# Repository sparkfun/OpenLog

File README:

OpenLog is an open source project to create a simple to use data logger. 

OpenLog v1 is stable but only supports FAT16 and up to 2GB.
OpenLog v2 is a bit buggy but supports FAT32 and SD cards up to 16GB.
OpenLog v3 is stable, supports FAT32 and supports higher record speeds (115200/57600).

The hardware design and firmware are released under CC-SA v3 license.
The FAT16/FAT32 firmware was originally designed by Roland Riegel and is released under GPL v2.
OpenLog v2.0 and above uses sdfatlib written by Bill Greiman and is released under GPL v3.
The OpenLog firmware was created by SparkFun Electronics.

v1.0 Buggy initial release
v1.1 Small changes to system settings and EEPROM storage.
v1.2 Added wild card to listing and remove commands. Added read file command.
v1.3 Added auto buffer record if unit sits idle for more than 5 seconds.
v1.4 Increase buffer size to 900 bytes. Pinning down URU errors.
v1.5 Lowered power consumption to ~2mA avg. Added 4800 and 19200 baud rates.
v1.51 Added configurable escape character, and escape character amount.
v1.6 Added ability to configure via config.txt file.
v2.0 Massive overhaul. Ported to sdfatlib. Now supports FAT16/FAT32/SD/SDHC.
v2.1 Power save not working. Fixed issue 35. Dropping characters at 57600bps.
v2.11 Tested with 16GB microSD. Fixed issues 30 & 34. Re-enable power save.
v2.2 Modified append_file() to use a single buffer. Increased HardwareSerial.cpp buffer to 512 bytes.
v2.21 ringp fork brought in. rm dir, cd .., and wildcards now work!
v2.3 Migrated to v10.10.10 of sdfatlib. Moved to inline RX interrupt and buffer.
v2.4 Merged ringp updates. Commands cd, rm, ls work again!
v2.41 Power loss bug fixed. Adding support for 38400bps for testing with SparkFum 9DOF IMU logging. 
v2.5 Added software reset command. Modified the read command to print extended ASCII characters.
v2.51 Changed command prompt control to ignore \n for easier control from microcontroller.
v3.0 Migration to Arduino v1.0 and better recording speed at 115200bps and 57600bps.

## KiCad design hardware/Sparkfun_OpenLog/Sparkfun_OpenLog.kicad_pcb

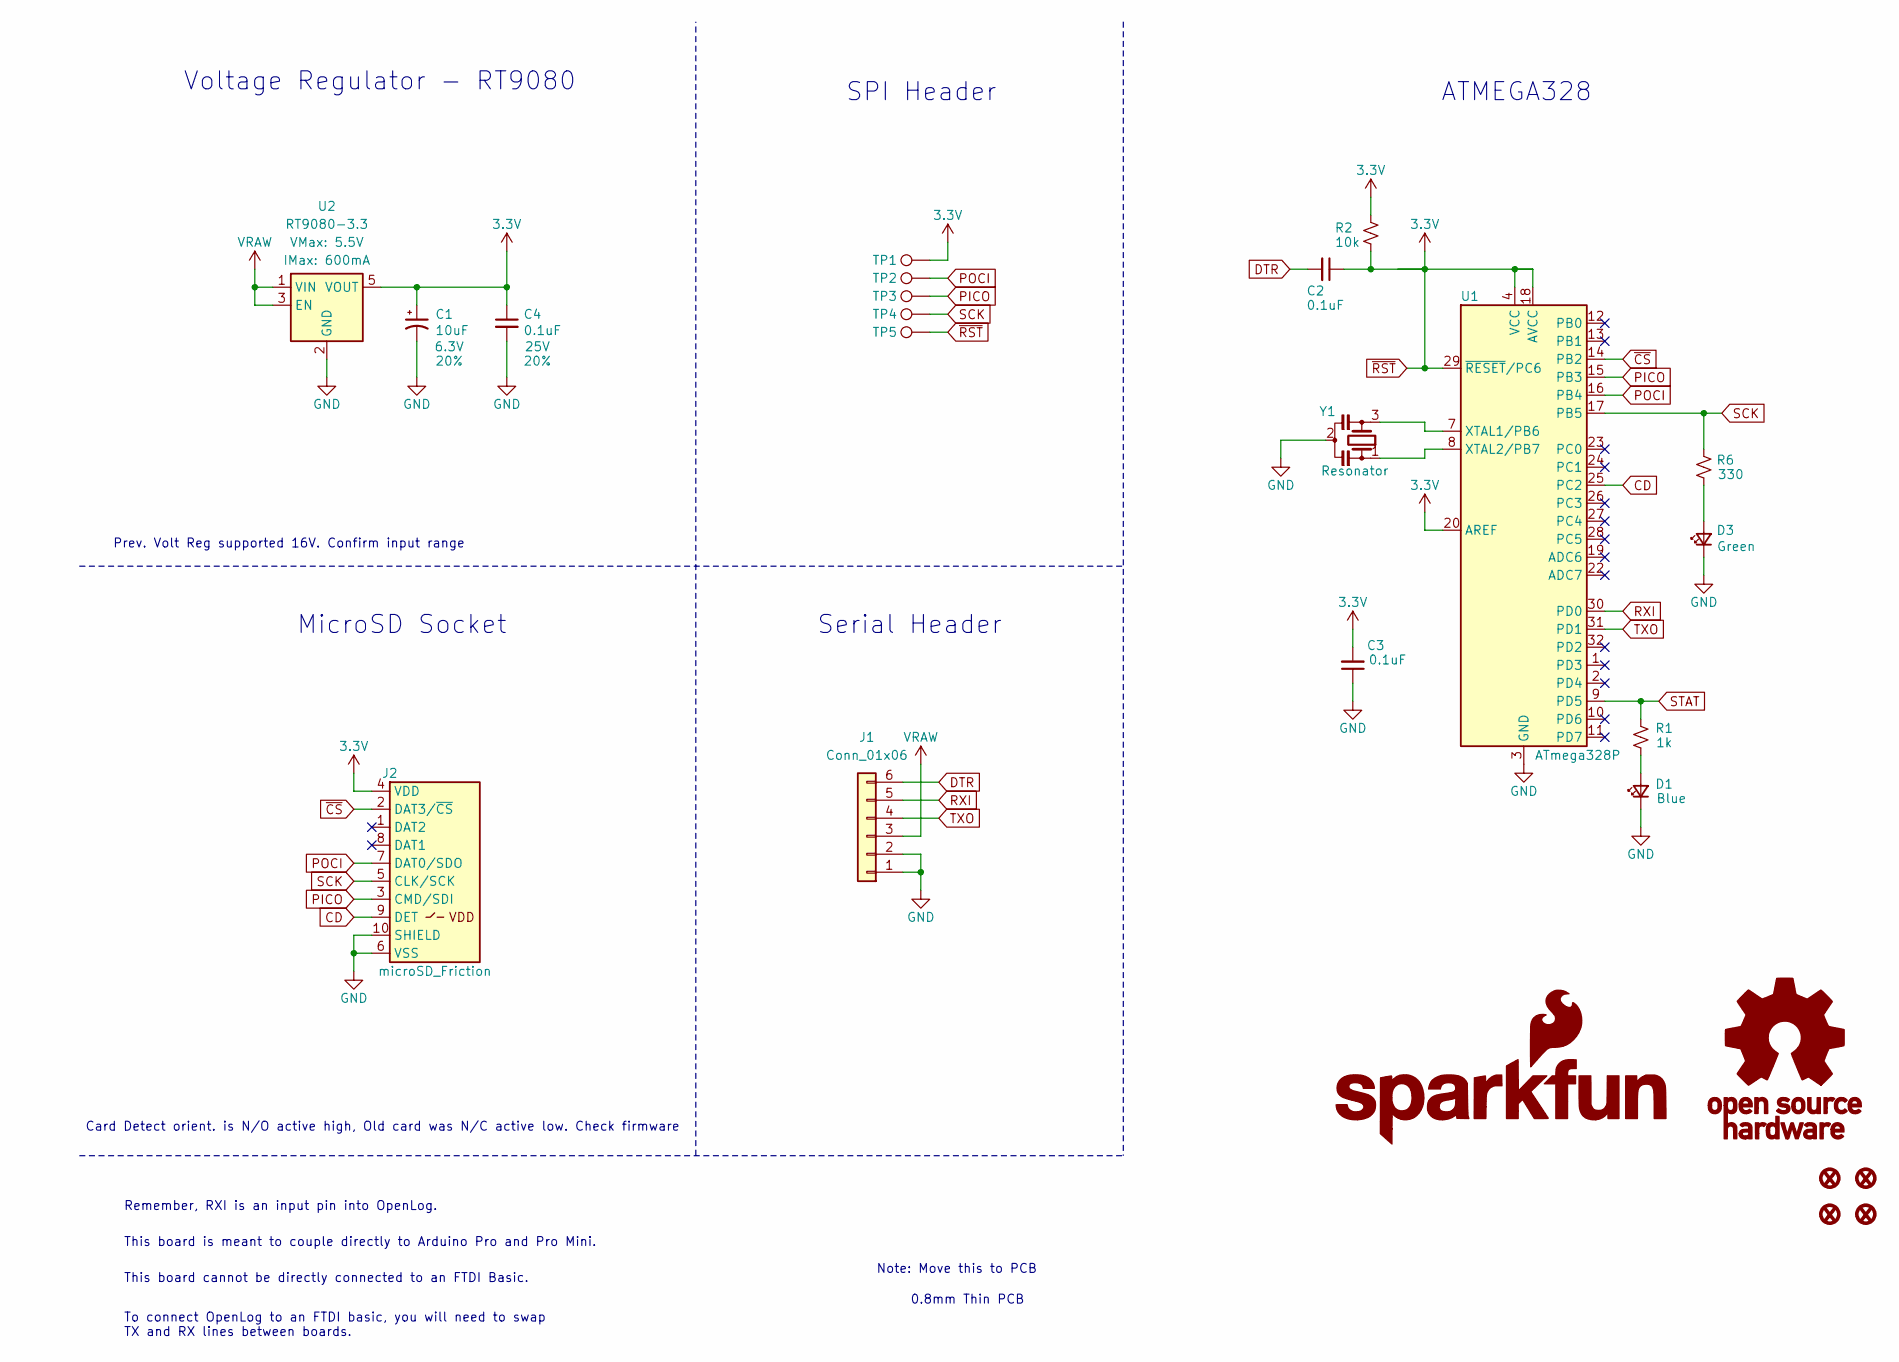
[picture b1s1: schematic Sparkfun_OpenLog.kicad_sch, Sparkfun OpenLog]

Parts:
C1: 10uF; C_0603_1608Metric_Polar; Voltage 6.3V; Tolerance 20%
C2, C3, C4: 0.1uF; C_0603_1608Metric; Voltage 25V; Tolerance 20%
D1: Blue; LED_0603_1608Metric_Blue
D3: Green; LED_0603_1608Metric_Green
FID1, FID2, FID3, FID4: Fiducial_0.5mm; Fiducial_0.5mm_Mask1mm
G1: OSHW_Logo; Creative_Commons_License
G2: SparkFun_Logo
J1: Conn_01x06; 1x06_P2.54mm
J2: microSD_Friction; microSD_Friction_Fit_Common
R1: 1k; R_0603_1608Metric
R2: 10k; R_0603_1608Metric
R6: 330; R_0603_1608Metric
TP1, TP2, TP3, TP4, TP5: 1.25mm; TestPoint-1.25mm
U1: ATmega328P; TQFP-32_7x7mm_P0.8mm
U2: RT9080-3.3; SOT23-5
Y1: Resonator; Resonator_SMD_3.2x1.3mm

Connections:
CD: J2.9 (DET), U1.25 (PC2)
DTR: C2.2, J1.6
GND: C1.2, C3.1, C4.2, D1.1 (K), D3.1 (K), J1.1, J1.2, J2.6 (VSS), J2.10 (SHIELD), U1.3 (GND), U1.5 (GND), U1.21 (GND), U2.2 (GND), Y1.2
unnamed: D1.2 (A), R1.2
unnamed: D3.2 (A), R6.2
unnamed: U1.7 (XTAL1/PB6), Y1.3
unnamed: U1.8 (XTAL2/PB7), Y1.1
PICO: J2.3 (CMD/SDI), TP3.1, U1.15 (PB3)
POCI: J2.7 (DAT0/SDO), TP2.1, U1.16 (PB4)
RXI: J1.5, U1.30 (PD0)
SCK: J2.5 (CLK/SCK), R6.1, TP4.1, U1.17 (PB5)
STAT: R1.1, U1.9 (PD5)
TXO: J1.4, U1.31 (PD1)
VRAW: J1.3, U2.1 (VIN), U2.3 (EN)
~CS: J2.2 (DAT3/~CS), U1.14 (PB2)
~RST: C1.1, C2.1, C3.2, C4.1, J2.4 (VDD), R2.1, R2.2, TP1.1, TP5.1, U1.4 (VCC), U1.6 (VCC), U1.18 (AVCC), U1.20 (AREF), U1.29 (~RESET/PC6), U2.5 (VOUT)

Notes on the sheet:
Remember, RXI is an input pin into OpenLog.
Card Detect orient. is N/O active high, Old card was N/C active low. Check firmware
Prev. Volt Reg supported 16V. Confirm input range
Note: Move this to PCB
0.8mm Thin PCB
Voltage Regulator - RT9080
MicroSD Socket
This board is meant to couple directly to Arduino Pro and Pro Mini.
This board cannot be directly connected to an FTDI Basic.
ATMEGA328
To connect OpenLog to an FTDI basic, you will need to swap TX and RX lines between boards.
SPI Header
Serial Header

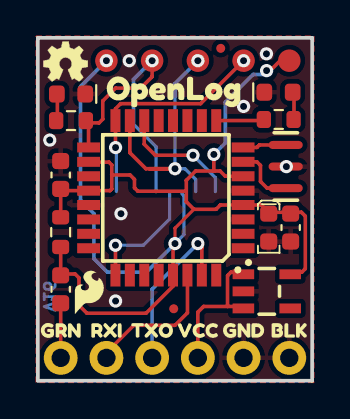
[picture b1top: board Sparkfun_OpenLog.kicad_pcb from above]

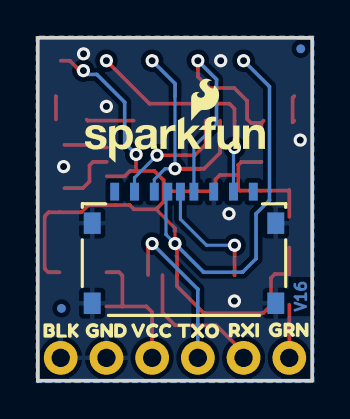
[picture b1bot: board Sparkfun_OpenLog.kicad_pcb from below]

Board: 2 copper layers, 15.2 x 19.0 mm, 38 parts (9 on the bottom side), 16 nets.

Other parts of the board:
Ref**: Val**; OSHW_Logo_2.5mm
kibuzzard-69F1223A, kibuzzard-69F1223A#2: G***; kibuzzard-69F1223A
kibuzzard-69F1224C, kibuzzard-69F1224C#2: G***; kibuzzard-69F1224C
kibuzzard-69F1225D, kibuzzard-69F1225D#2: G***; kibuzzard-69F1225D
kibuzzard-69F1226C, kibuzzard-69F1226C#2: G***; kibuzzard-69F1226C
kibuzzard-69F12217, kibuzzard-69F12217#2: G***; kibuzzard-69F12217
kibuzzard-69F12278, kibuzzard-69F12278#2: G***; kibuzzard-69F12278
kibuzzard-69F12315: G***; kibuzzard-69F12315

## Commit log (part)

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2009-12-23 Test commit
2009-12-23 Posting main source
2009-12-24 Adding Eagle Files and some directory structure
2009-12-28 v1.1 - Fixes over-run resets and adds NewLog and SeqLog functions. Added lots-o-text.txt for testing.
2010-02-18 Split out the cluster offset calcuation to avoid a signed/unsigned 16x16 multiply breaking over 32k. I.E. create and set a u32, multiply it by the signed (sizeof), then add the offset.
2010-03-17 Added support for extended read command. The read command now accepts parameters for file position and number of characters to read.
2010-03-18 Version number (v1.2) to main.c. The number of write cycles to EEPROM minimized in order not to wear out the EEPROM memory. Other comment changes.
2010-03-23 Using "init" command to initialize the SD card will not reset file system handles stored in global arrays in fat.c. Calling "init" several times will cause other commands to stop working, like "cd <f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
2010-03-24 v1.3 Added sd_raw_sync() inside append_file. I believe this was why tz1's addition of the timeout buffer update feature was not working. Auto buffer update now working. So if you don't send anything 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
2010-03-31 v1.4 Eliminates errors while logging at 57600bps. Added exit options to the two menus (set and baud) Also added display of current settin to two menus (Ex: "Baud currently: 57600bps")
    Added '!' infront of 'error opening'. This pops up if there is an error while trying to append to a freshly created new log (ex: LOG00548.txt is created, then errors out because it cannot append). '!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
    Replicated logging errors at 57600 using 5V Arduino
    Unit would systematically glitch during logging of 111054 bytes
    Increasing buffer to 1000 characters caused URU error.
    URU: Unit Resets Unexpectedly
    To recreate URU error. Type "append ". Include the space. If you g
2010-04-07 v1.5 Added 4800bps and 19200bps support
    Added power saving features. Current consumption at 5V is now:
    In default append mode:
    6.6/5.5mA while receiving characters (LED On/Off)
    2.1mA during idle
    In command mode: 3.2/2.1mA (LED On/Off)
    So if you're actively throwing characters at the logger, it will be ~6mA. If you send the logger characters then delay 5-10 seconds, current will be ~2.5mA. (Unit records the characters in the buffer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
2010-04-21 v1.6 Adding config file. OpenLog can now be configured either through CONFIG.txt or through system menus.
    What happens if I reset the system by pulling RX low, but the config file has corrupt values in it? If config file has corrupt values in it, system will default to known values 9600/ctrl+z/3/newlog. 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
2010-06-01 Support for using OpenLog with Parallax Javelin Stamp. Simplified set of commands -that can be used with any other micro processor- to count files in a folder (efcount), get file info (efinfo), turn 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
2010-06-03 Fix for disabling the logging of escape character ASCII 26 (Ctrl+z). When appending to a file the escape character currently used will also be appended to the file. In order to avoid this problem iss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
2010-06-07 Fixed timing issue in OpenLog.java. Removed unnecessary delay in openLogExecute().
2010-08-04 v2.1 - Fixed issue 35. Dropping characters at 57600bps. Power save not working.
    26058 bytes out of 30720
    Fixed a bug found by Salient (Issue 35). User settings where declared at chars which allowed them to be signed. If a user went from old firmware, to v2, the safety checks would fail because the setti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
    Added "a) Clear user settings" to set menu. This allows us to completely wipe an OpenLog (user settings and config file) to see how it will respond to future firmware changes.
    Improved the file 'size' command.
    Sequential logging is tested and works.
    Receive testing: Using the Test_Sketch found on Github, I
2010-08-18 v2.11 Tested with 16GB microSD. Fixed some general bugs. Lowered power consumption.
    26136 bytes out of 30720
    Fixed issue 30. I added printing a period ('.') for non-visible ASCII characters during a 'read' command. This cleans up the output a bit. HEX printing is still available.
    Fixed issue 34. When issuing a long command such as "read log00056.txt 100 200 2" (read from spot 100 to spot 200 and print in HEX), the command shell would die at 24 spots. I increased both the gene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
    Works with a 16GB microSD card! High volume test: loaded 16GB card with 5GB of
2010-09-21 Makefile changes. Not to be commited upstream.
2010-09-26 Added support for removing an empty folder using "rm -f" command. Listing the contents of a folder lists the subfolders first and then the files in the folder.
2010-10-03 Fixed "888 88" bug when hitting backspace. Resolved ambigous "rm" command, new "rm" implementation. New commands: pwd (print working directory), echo <on>|<off>. Fixed bug when using "size", leaking 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
2010-10-27 Added .gitignore to ignore *.class and *.jpf files.
2010-11-03 v2.4 Merged ringp updates. Commands cd, rm, ls work again! New "rm -rf" command to remove directory and its files.
    Windows 7 stores the Arduino hex file is an aweful place. Something like:
    C:\Users\Main\AppData\Local\Temp\build3390340147786739225.tmp\OpenLog_v2.cpp.hex
    Added HardwareSerial.cpp and a readme to the main trunk.
    Added OpenLog_v2.cpp.hex to the main trunk.
2010-11-03 Missing HardwareSerial.h needed by HardwareSerial.cpp
    New function declarations in the HardwareSerial class needs the functions
    to be declarared in the h-file. This commit contains a modified version of the
    original HardwareSerial.h file.
2011-06-01 v2.51 Improved command prompt parsing (now ignores '\n')
    We now ignore the \n character when parsing characters from the command prompt. This makes it easier to create code on a microcontroller that correctly controls OpenLog. Previously, println or sprint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
    sprintf(buff, "new blah.txt\r");
    Serial.print(buff); //No println, use \r in string instead
    Also - added a CommandTest sketch to demonstrate how you can control OpenLog from a microcontroller / automate the command prompt
2012-02-06 make sure escape characters don't end up in the file in append mode (fixes: https://github.com/nseidle/OpenLog/issues/92 )
2012-02-22 Updated the CommandTest code to Arudino v1.0. I had to change the Serial.print(char(26)) to Serial.write(26). Also added more comments to top of code. File is now .ino.
2012-02-26 added "mv" aka "rename" support to openlog; backported from a more recent fatlib
2012-03-14 v3.0 Re-write of core functions. Support under Arduino v1.0. Now supports full speed 57600 and 115200bps! Lower standby power. 28354 bytes out of 32256. Update to new beta version of SerialPort lib f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
    Unzip 'SerialPortBeta20120106.zip' and
2012-03-16 v3.1 28692 of 32256 Added fix from issue 76: https://github.com/nseidle/OpenLog/issues/76 Added support for verbose and echo settings recorded to the config file and EEPROM.
2012-03-23 v3.1 Fixed bug where entire log data is lost when power is lost. Added fix from issue 76: https://github.com/nseidle/OpenLog/issues/76 Added support for verbose and echo settings recorded to the conf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
2012-03-27 v3.11 Added freeMemory support for RAM testing. This was taken from: http://arduino.cc/playground/Code/AvailableMemory Also updated HEX files for v3.11 and v3 Light
2013-01-08 Changes to attempt to free up RAM.
    Added printRam/freeRam function from Jeelabs. Many more F() uses.
    new_file now exits before it calls append_file. Removed global Sf file
    in an attempt to free up RAM. Didn't really help. Removed helper line
    from the config file. We need to bring this back but I'm not sure how.
2013-01-08 v3.13 Lots of RAM management. Works well.
    Receive buffer returned to its glory of being around 800 bytes. This is
    very good news. Changed the string compares from strings in RAM (strcmp)
    to strings located in flash memory(strcmp_P). Removal of strncmp(). Once
    migrated to PSTR, it makes it worse. Issue 106 was the key to all this.
2013-01-14 Better handling of max time before sync.
    There is a case where the user could be throwing non-stop data at the
    unit. The log won't be recorded because it never goes idle. This version
    adds/makes better the check of max time for the un-recorded buffer. Also
    moved from sprintf_P to strcpy_P for known file names.
2013-01-15 Cleaned up the help menu.
2013-01-21 Added a fix for issue 132
    Sending lots of binary, fast, causes the escape character to not
    properly get reset. Added a secondary reset of escape_chars_received to
    reset it. Works well. Also added a binary test sketch to test OpenLogs
    with binary at 115200bps.
2013-03-07 porting readme to markdown and prettyfying
2013-03-07 Cleanup readme files.
2013-03-14 Updated the .hex files to reflect v3.14 changes
    Created new COMBINED .hex file (bootloader and v3.14 sketch) and updated
    OpenLog_v3.cpp.hex to be consistent with v3.14
2013-04-08 Added ability to ignore RX.
    You can now ignore the state of RX at power up. See issue #150.
2013-04-08 Fixed rm issue #134. dlkeng is my new favorite person.
    Fixed issue #135: When removing files and there is a directory, all
    wildcard files are now removed correctly. Thank you dlkeng! Your patch
    worked great!
2013-04-09 Updated readme and added fritzing image.
2013-07-16 Fix array size bug that caused echo to fail.
    The array size was too small which caused echo to act oddly and it
    caused the config file record to corrupt the file. This would show
    itself when the SD was read on a computer and windows would insist on
    scanning and fixing.
2013-07-16 Added feature: no new file if old file is zero bytes.
    See issue #136. Thank you dlkeng! You rock. Again. Thanks for adding
    this feature. When starting in new log mode, if the LOG00256.txt is zero
    bytes, OpenLog will use LOG00256 instead of LOG00257.
2013-07-16 Removed a fixed length array from Light version.
2013-09-23 Added 'disk' checking in the read example sketch.
    Related to issue 158.
2013-12-14 Increased number of escape chars, log name increment and memory bug.
    The number of escape chars was increased to 0 to 254. The log name now
    increments even if there are no files and the receive buffer was
    decreased to prevent memory bugs.
2013-12-14 Increase local buffer to 128 bytes
    After testing increasing the local buffer to 128 helped maintain
    constant record at 115200bps.
2014-07-14 createFile() variable name issue
    I was trying to get the code to work using the v2.51 code, but it would not verify. Found out that "OpenLog.println(filename);" on line 127, 159, and 206, needed to be "fileName," not "filename."
2014-08-04 Adding required libraries.
    If there's a better way to add support for dependencies please let me
    know. I would just hate to loose access to this lib in the future. And
    finding it/installing it seems to be problematic for users (see issue
    171).
2014-08-11 Re-write large file example to report without character errors.
    This example reads characters from OpenLog over the hardware serial at
    9600 and passes them out over the software serial at 14400. This is
    needed for issue 170.
2015-05-31 Fixed returning pointer to local array.
2015-10-31 Reset nextlog count when seqlog option is used.
2015-11-24 Now compiles under Arduino v1.6.x. A large number of changes. See CHANGELOG
    Significant changes to reduce RAM footprint. Updated to most recent
    SdFatlib-beta.
2015-11-25 Updating changelog. Removing extraneous code from OpenLog_Minimal.
2015-11-25 Best performance at 512/256 RAM split. Fixed odd zero newlog EEPROM glitch.
2015-12-01 Change to smaller OSHW logo. Moved top copper fiducials.
2016-01-26 Remove/approve dimensional warnings.
2016-01-27 created panel v15
2016-01-28 recreated panel v15
2016-03-21 Resolved the merge conflict
    I think Bob moved some fiducials (good) and I failed to bring in his
    changes before submitting resistor change. All fixed. Should not affect
    his panel because it's just a part_id change on the schematic.
2016-04-07 Updating directory structure, updating fritzing documentation
2016-10-11 Updating serialport lib to work with recent Arduino releases.
    Fixes issue 204.
2018-02-09 Fix verbose bug issue 208
2018-04-30 Driving SPI pins low to avoid power consumption on some SD cards. See issue 215.
2018-11-28 Fix echo and verbose bug in issue #224.
2020-01-21 Update README.md
    - Updating missing image
    - Link OpenLog with Headers
2021-10-12 Typo fixes
2021-10-14 Add binaries and bootload tools.

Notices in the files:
hardware/Sparkfun_OpenLog/Sparkfun_OpenLog.kicad_pcb:
Released under the Creative Commons
https://creativecommons.org/licenses/by-sa/4.0
